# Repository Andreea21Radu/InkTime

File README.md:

# InkTime - Smartwatch PCB Design

**Autor:** Radu Andreea
**Licenta:** Apache License 2.0 

## 1. Arhitectura sistemului

Sistemul este construit in jurul microcontroller-ului **nRF52840**, care gestioneaza comunicatia si perifericele.

Structura generala este urmatoarea:

## 2. BOM (Bill of Materials)

## CIRCUITE INTEGRATE (IC)

| Componentă | JLC Part # | Package | Descriere | Datasheet |
| :--- | :--- | :--- | :--- | :--- |
| IC1 | C3682423 | DSBGA-8 (1.6x1.1) | Încărcător baterie Li-Ion / Li-Polymer | [datasheet](https://www.ti.com/cn/lit/ds/symlink/bq25180.pdf) |
| IC2 | C81079 | DSBGA-9 | Driver haptic ERM/LRA | [datasheet](https://www.ti.com/cn/lit/gpn/drv2605) |
| IC3 | C189517 | LGA-12 (2x2) | Accelerometru 3 axe low-g 12bit | [datasheet](https://www.lcsc.com/datasheet/C189517.pdf) |
| IC9 | C7065276 | WLCSP-15B (2.3x1.4) | DC-DC buck-boost regulator I2C | [datasheet](https://wmsc.lcsc.com/wmsc/upload/file/pdf/v2/lcsc/2312271436_Richtek-Tech-RT6160AWSC_C7065276.pdf) |
| U1 | C3606653 | QFN-48 (6x6) | nRF52840 MCU | [datasheet](https://www.lcsc.com/datasheet/C3606653.pdf) |
| U2 | C2682616 | DFN-8-EP (2x2) | Fuel gauge baterie Li-Ion I2C | [datasheet](https://www.lcsc.com/datasheet/lcsc_datasheet_2410121738_Analog-Devices-Inc--Maxim-Integrated-MAX17048G-T10_C2682616.pdf) |

---

## CONECTORI

| Componentă | JLC Part # | Package | Descriere | Datasheet |
| :--- | :--- | :--- | :--- | :--- |
| J1 | C122434 | SMD, FFC/FPC 0.5mm | Conector FPC 24 pini, unghi drept | [datasheet](https://www.molex.com/content/dam/molex/molex-dot-com/products/automated/en-us/salesdrawingpdf/503/503480/5034802400_sd.pdf) |
| J2 | C90533 | 1mm pitch | Adaptor cablu 6 poziții | [datasheet](https://wmsc.lcsc.com/wmsc/upload/file/pdf/v2/lcsc/1810141506_LX-FFC6P1-0mm7CM_C90533.pdf) |
| J4 | C709357 | USB-C SMD | Conector USB Type-C 16P | [datasheet](https://www.lcsc.com/datasheet/lcsc_datasheet_2404191039_Shenzhen-Kinghelm-Elec-KH-TYPE-C-16P_C709357.pdf) |

---

## SEMICONDUCTORI

| Componentă | JLC Part # | Package | Descriere | Datasheet |
| :--- | :--- | :--- | :--- | :--- |
| Q1 | C2564 | TO-220AB | MOSFET P-channel 55V 74A | [datasheet](https://www.lcsc.com/datasheet/lcsc_datasheet_1809041724_Infineon-Technologies-IRF4905PBF_C2564.pdf) |
| Q3 | C469327 | SOT-323 | MOSFET N-channel 30V 1.5A | [datasheet](https://www.lcsc.com/datasheet/lcsc_datasheet_1912202016_Vishay-Intertech-SI1308EDL-T1-GE3_C469327.pdf) |
| D2, D4, D5 | C82046 | SOD-123 | Diodă Schottky 0.5A 30V | [datasheet](https://www.lcsc.com/datasheet/lcsc_datasheet_2304140030_onsemi-MBR0530T1G_C82046.pdf) |
| D3 | C2969755 | SOT-23-6L | Protecție ESD USB | [datasheet](https://wmsc.lcsc.com/wmsc/upload/file/pdf/v2/lcsc/2211080730_STMicroelectronics-USBLC6-2SC6Y_C2969755.pdf) |

---

## INDUCTORI

| Componentă | JLC Part # | Package | Descriere | Datasheet |
| :--- | :--- | :--- | :--- | :--- |
| L1, L2, L3 | C12669 | 0402 | Inductor general (chip inductor) | [datasheet](https://www.lcsc.com/datasheet/lcsc_datasheet_2304140030_Murata-Electronics-LQG15HS27NJ02D_C12669.pdf) |
| L5 | C1329646 | SMD 4.8x4.8mm | Power inductor 4.7µH 1.6A | [datasheet](https://wmsc.lcsc.com/wmsc/upload/file/pdf/v2/lcsc/2304140030_BOURNS-SRR4828A-4R7Y_C1329646.pdf) |
| L7 | C5832368 | 1008 | Power inductor 470nH 6.5A | [datasheet](https://wmsc.lcsc.com/wmsc/upload/file/pdf/v2/lcsc/2306021632_cjiang--Changjiang-Microelectronics-Tech-FTC252012SR47MBCA_C5832368.pdf) |

---

## CRISTALE

| Componentă | JLC Part # | Package | Descriere | Datasheet |
| :--- | :--- | :--- | :--- | :--- |
| X1 | C9009 | SMD3225-4P | Cristal Oscilator 32 MHz | [datasheet](https://www.lcsc.com/datasheet/lcsc_datasheet_2403291504_YXC-Crystal-Oscillators-X322532MOB4SI_C9009.pdf) |
| X2 | C32346 | SMD3215-2P | Cristal Oscilator 32.768 kHz | [datasheet](https://www.lcsc.com/datasheet/lcsc_datasheet_2404180925_Seiko-Epson-Q13FC13500004_C32346.pdf) |

---

## REZISTOARE

| Componentă | JLC Part # | Package | Descriere | Datasheet |
| :--- | :--- | :--- | :--- | :--- |
| R1_EP_DR | C3920633 | 0201 | 7.68kΩ Thin Film ±0.5% | [datasheet](https://wmsc.lcsc.com/wmsc/upload/file/pdf/v2/lcsc/2404081048_TE-Connectivity-CPF0201B511RE1_C3920633.pdf) |
| R1_USB, R2_USB | C3920633 | 0201 | 7.68kΩ Thin Film ±0.5% | [datasheet](https://wmsc.lcsc.com/wmsc/upload/file/pdf/v2/lcsc/2404081048_TE-Connectivity-CPF0201B511RE1_C3920633.pdf) |
| R2, R3, R4 | C3920633 | 0201 | 7.68kΩ Thin Film ±0.5% | [datasheet](https://wmsc.lcsc.com/wmsc/upload/file/pdf/v2/lcsc/2404081048_TE-Connectivity-CPF0201B511RE1_C3920633.pdf) |
| R2_EP_DR, R9, R_PWR_EPD | C3920633 | 0201 | 7.68kΩ Thin Film ±0.5% | [datasheet](https://wmsc.lcsc.com/wmsc/upload/file/pdf/v2/lcsc/2404081048_TE-Connectivity-CPF0201B511RE1_C3920633.pdf) |
| R5, R7, R8 | C3920633 | 0201 | 7.68kΩ Thin Film ±0.5% | [datasheet](https://wmsc.lcsc.com/wmsc/upload/file/pdf/v2/lcsc/2404081048_TE-Connectivity-CPF0201B511RE1_C3920633.pdf) |
| R17, R18 | C3920633 | 0201 | 7.68kΩ Thin Film ±0.5% | [datasheet](https://wmsc.lcsc.com/wmsc/upload/file/pdf/v2/lcsc/2404081048_TE-Connectivity-CPF0201B511RE1_C3920633.pdf) |
| R_TYPE_SEL | C3920633 | 0201 | 7.68kΩ Thin Film ±0.5% | [datasheet](https://wmsc.lcsc.com/wmsc/upload/file/pdf/v2/lcsc/2404081048_TE-Connectivity-CPF0201B511RE1_C3920633.pdf) |

---

## CAPACITORI

| Componentă | JLC Part # | Package | Descriere | Datasheet |
| :--- | :--- | :--- | :--- | :--- |
| C1, C2, C17, C18 | C9900156064 | 0201 | Generic chip capacitor | [datasheet](https://ds.yuden.co.jp/TYCOMPAS/or/download?pn=MLAST063SCG681JFNA01&fileType=CA) |
| C1-EP-DR | C9900156064 | 0201 | Generic chip capacitor | [datasheet](https://ds.yuden.co.jp/TYCOMPAS/or/download?pn=MLAST063SCG681JFNA01&fileType=CA) |
| C2-EP-DR | C9900156064 | 0201 | Generic chip capacitor | [datasheet](https://ds.yuden.co.jp/TYCOMPAS/or/download?pn=MLAST063SCG681JFNA01&fileType=CA) |
| C3, C4 | C9900156064 | 0201 | Generic chip capacitor | [datasheet](https://ds.yuden.co.jp/TYCOMPAS/or/download?pn=MLAST063SCG681JFNA01&fileType=CA) |
| C5, C7, C8, C12, C19 | C9900156064 | 0201 | Generic chip capacitor | [datasheet](https://ds.yuden.co.jp/TYCOMPAS/or/download?pn=MLAST063SCG681JFNA01&fileType=CA) |
| C6, C14, C20, C21 | C9900156064 | 0201 | Generic chip capacitor | [datasheet](https://ds.yuden.co.jp/TYCOMPAS/or/download?pn=MLAST063SCG681JFNA01&fileType=CA) |
| C9 | C9900156064 | 0201 | Generic chip capacitor | [datasheet](https://ds.yuden.co.jp/TYCOMPAS/or/download?pn=MLAST063SCG681JFNA01&fileType=CA) |
| C10, C13, C22 | C9900156064 | 0201 | Generic chip capacitor | [datasheet](https://ds.yuden.co.jp/TYCOMPAS/or/download?pn=MLAST063SCG681JFNA01&fileType=CA) |
| C11 | C9900156064 | 0201 | Generic chip capacitor | [datasheet](https://ds.yuden.co.jp/TYCOMPAS/or/download?pn=MLAST063SCG681JFNA01&fileType=CA) |
| C15 | C9900156064 | 0201 | Generic chip capacitor | [datasheet](https://ds.yuden.co.jp/TYCOMPAS/or/download?pn=MLAST063SCG681JFNA01&fileType=CA) |
| C16 | C9900156064 | 0201 | Generic chip capacitor | [datasheet](https://ds.yuden.co.jp/TYCOMPAS/or/download?pn=MLAST063SCG681JFNA01&fileType=CA) |
| C23, C27, C34, C42 | C21012218 | 0402 | Capacitor ceramic | [datasheet](https://jlc-prod-smt.oss-eu-central-1.aliyuncs.com/smtDataManualFile/8603520985945550848-C21012218.pdf) |
| C24, C39 | C9900179830 | 0402 | Capacitor ceramic | N/A |
| C25, C33 | C9900179830 | 0402 | Capacitor ceramic | N/A |
| C29, C30, C31, C32, C37, C38 | C3920633 | 0201 | Capacitor ceramic | [datasheet](https://ds.yuden.co.jp/TYCOMPAS/or/download?pn=MLAST063SCG681JFNA01&fileType=CA) |
| C43 | C9900156064 | 0201 | Generic chip capacitor | [datasheet](https://ds.yuden.co.jp/TYCOMPAS/or/download?pn=MLAST063SCG681JFNA01&fileType=CA) |
| EPD_C1, EPD_C2, EPD_C6, EPD_C7, EPD_C8, EPD_C9, EPD_C10, EPD_C11, EPD_C12 | C9900156064 | 0201 | Generic chip capacitor | [datasheet](https://ds.yuden.co.jp/TYCOMPAS/or/download?pn=MLAST063SCG681JFNA01&fileType=CA) |
| EPD_C5 | C9900156064 | 0201 | Generic chip capacitor | [datasheet](https://ds.yuden.co.jp/TYCOMPAS/or/download?pn=MLAST063SCG681JFNA01&fileType=CA) |

---

## ALTE COMPONENTE

| Componentă | JLC Part # | Package | Descriere | Datasheet |
| :--- | :--- | :--- | :--- | :--- |
| ANT1 | C2917717 | 1206 | Antenă Patch 2.4 GHz | [datasheet](https://www.lcsc.com/datasheet/lcsc_datasheet_2404021210_Johanson-Dielectrics-2450AT18B100E_C2917717.pdf) |
| SJ1 | N/A | Solder Jumper | SMD solder JUMPER (leave open) | N/A |
| SW_DN, SW_ENT, SW_UP | C569760 | SMD 3.9x2.9mm | Buton tactil SPST (Tactile Switch) | [datasheet](https://wmsc.lcsc.com/wmsc/upload/file/pdf/v2/lcsc/2301111010_PANASONIC-EVPAKE31A_C569760.pdf) |
| TP (Test Pads) | N/A | N/A | Puncte de testare (Test pads) | N/A |

## 3. Functionalitate hardware si specificatii tehnice

Proiectul **InkTime** reprezinta un dispozitiv wearable optimizat pentru consum redus de energie, capabil sa functioneze pe perioade lungi de timp datorita combinatiei dintre un microcontroller eficient si un display E-Ink, care consuma energie doar la actualizare.

---

### 3.1 Unitatea centrala (Microcontroller)

In centrul sistemului se afla circuitul **nRF52840**, care integreaza toate functiile principale:

* Procesor **ARM Cortex-M4F la 64 MHz**, suficient pentru procesare de semnale si control periferice
* Suport integrat pentru **Bluetooth Low Energy (BLE)**, utilizat pentru comunicarea cu telefonul
* Moduri de consum redus (sleep si deep sleep), unde curentul scade pana la nivel de microamperi

Acest microcontroller permite rularea simultana a comunicatiei wireless si a interactiunii cu senzorii, mentinand consumul scazut.

### 3.2 Sistem de alimentare

Alimentarea este realizata printr-un lant complet de power management:

* **BQ25180** – responsabil pentru incarcarea bateriei Li-Po prin USB-C, folosind metoda CC/CV si protectii integrate
* **RT6160** – convertor buck-boost care asigura o tensiune stabila de **3.3V**, chiar daca bateria scade sub aceasta valoare
* **MAX17048** – circuit de monitorizare a bateriei, care transmite starea de incarcare catre microcontroller prin I2C

Avantajul folosirii convertorului buck-boost este utilizarea eficienta a bateriei pe intreaga plaja de tensiuni.

### 3.3 Comunicatia intre module

Pentru conectarea componentelor, sistemul foloseste doua interfete principale:

#### Magistrala I2C

Este utilizata pentru perifericele inteligente:

* accelerometrul (IMU)
* fuel gauge-ul
* driverul haptic

Toate aceste componente sunt conectate pe aceeasi magistrala, ceea ce reduce numarul de pini folositi si simplifica traseele pe PCB.

#### Magistrala SPI

Este dedicata exclusiv display-ului:

* display-ul E-Ink este conectat prin SPI folosind conectorul FPC
* aceasta interfata permite transfer rapid de date necesar actualizarii imaginii

### 3.4 Interactiune cu utilizatorul

Dispozitivul include:

* 3 butoane pentru navigare (UP, ENTER, DOWN)
* feedback haptic realizat cu **DRV2605**, controlat prin PWM

Acest sistem permite interactiune intuitiva fara consum mare de energie.

### 3.5 Estimarea consumului de energie

Sistemul este alimentat de o baterie Li-Po de aproximativ **250 mAh**.

Consum estimat:

* Sleep (MCU + BLE): ~35 µA
* Functionare activa (citire senzori): ~120 µA
* Actualizare display: ~25 µA

Curent mediu total:

I_avg ≈ 180 µA = 0.18 mA

### 3.6 Autonomie estimata

Autonomia teoretica:

T = 250 mAh / 0.18 mA ≈ 1380 ore

In conditii reale (BLE, senzori, vibratii):

👉 aproximativ **9 – 14 zile**

## 4. Mapare pini nRF52840

### 4.1 Alocarea pinilor

| Componenta    | Semnal | Pin nRF | Directie | Motiv                |
| ------------- | ------ | ------- | -------- | -------------------- |
| Display E-Ink | SCK    | P0.11   | Output   | Clock SPI            |
| Display E-Ink | MOSI   | P0.12   | Output   | Transfer date        |
| Display E-Ink | CS     | P0.13   | Output   | Selectie dispozitiv  |
| Display E-Ink | DC     | P0.14   | Output   | Data / Command       |
| Display E-Ink | RESET  | P0.15   | Output   | Reset hardware       |
| Display E-Ink | BUSY   | P0.16   | Input    | Status display       |
| I2C           | SDA    | P0.26   | I/O      | Linie date           |
| I2C           | SCL    | P0.27   | Output   | Linie clock          |
| Buton UP      | GPIO   | P1.07   | Input    | Navigare             |
| Buton ENTER   | GPIO   | P1.08   | Input    | Confirmare           |
| Buton DOWN    | GPIO   | P1.09   | Input    | Navigare             |
| Motor haptic  | PWM    | P1.02   | Output   | Control vibratii     |
| RT6160        | EN     | P0.18   | Output   | Activare convertor   |
| IMU           | INT    | P0.25   | Input    | Intrerupere hardware |

---

### 4.2 Decizii de design

* **Port 0** a fost folosit pentru interfete rapide (SPI, I2C)
* **Port 1** a fost folosit pentru butoane, pentru a evita interferente
* pinii SPI au fost grupati fizic pentru trasee mai scurte
* magistrala I2C este comuna pentru mai multe dispozitive → economie de pini
* pinii NFC (P0.09, P0.10) au fost evitati pentru extensii viitoare

## 5. Design log si decizii de implementare

### 5.1 Layout PCB

* componentele au fost plasate compact
* traseele de alimentare au fost facute la **0.3 mm**
* traseele de semnal la **0.15 mm**
* zona antenei a fost lasata fara cupru

### 5.2 Probleme si solutii

* componente 0201 → necesare pentru spatiu redus
* routing dificil sub MCU → s-au folosit trasee mai subtiri local
* antena → zona keep-out pentru performanta RF

### 5.3 Integritate semnal

* condensatori de decuplare (100nF) plasati foarte aproape de pini
* GND realizat cu polygon pour pe ambele straturi
* via stitching pentru masa

## 6. Randari si imagini

(Imaginile se gasesc in folderul `Images`)

* vedere PCB top
* vedere PCB bottom
* randare 3D
* vedere explodata

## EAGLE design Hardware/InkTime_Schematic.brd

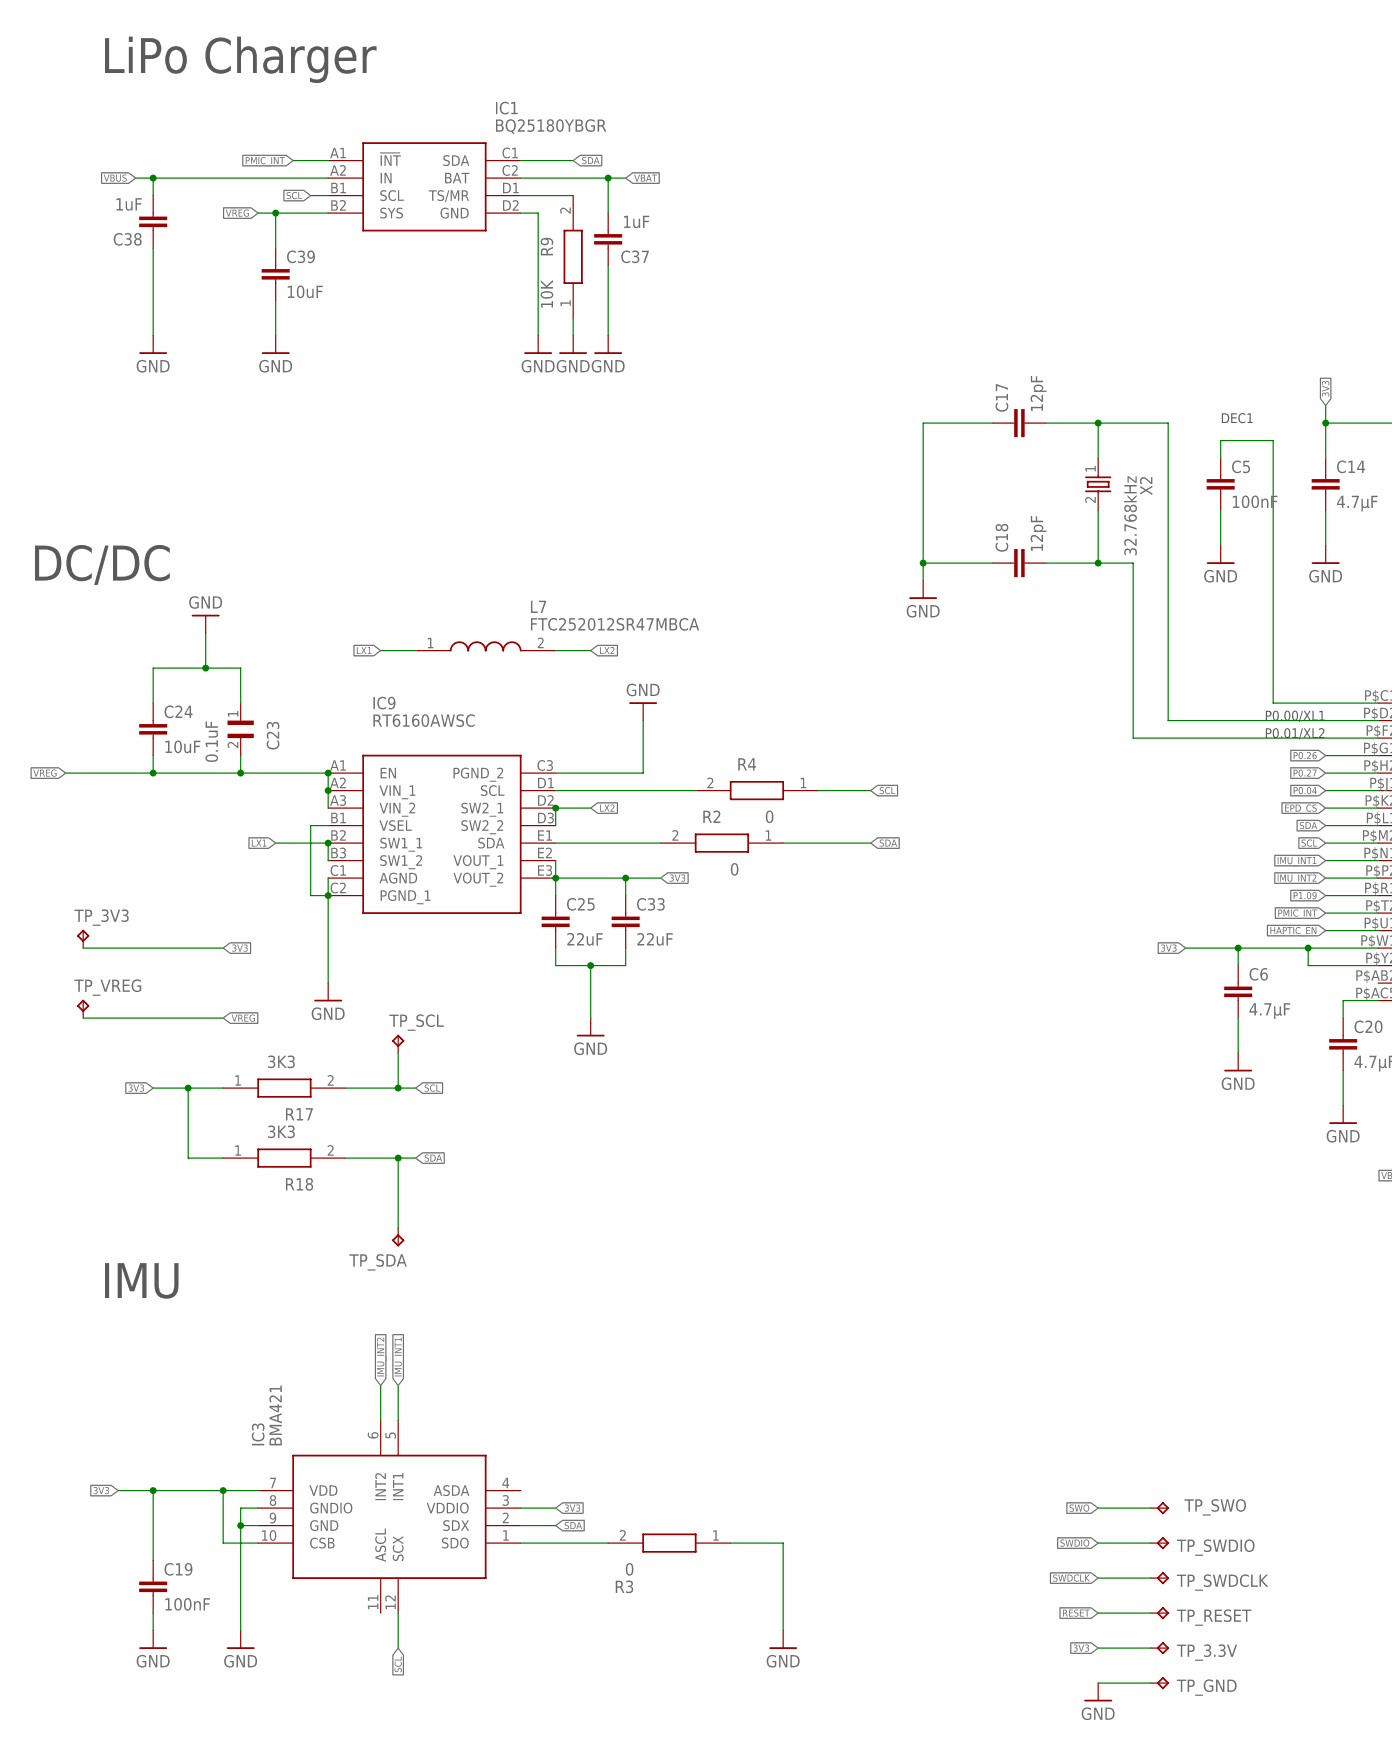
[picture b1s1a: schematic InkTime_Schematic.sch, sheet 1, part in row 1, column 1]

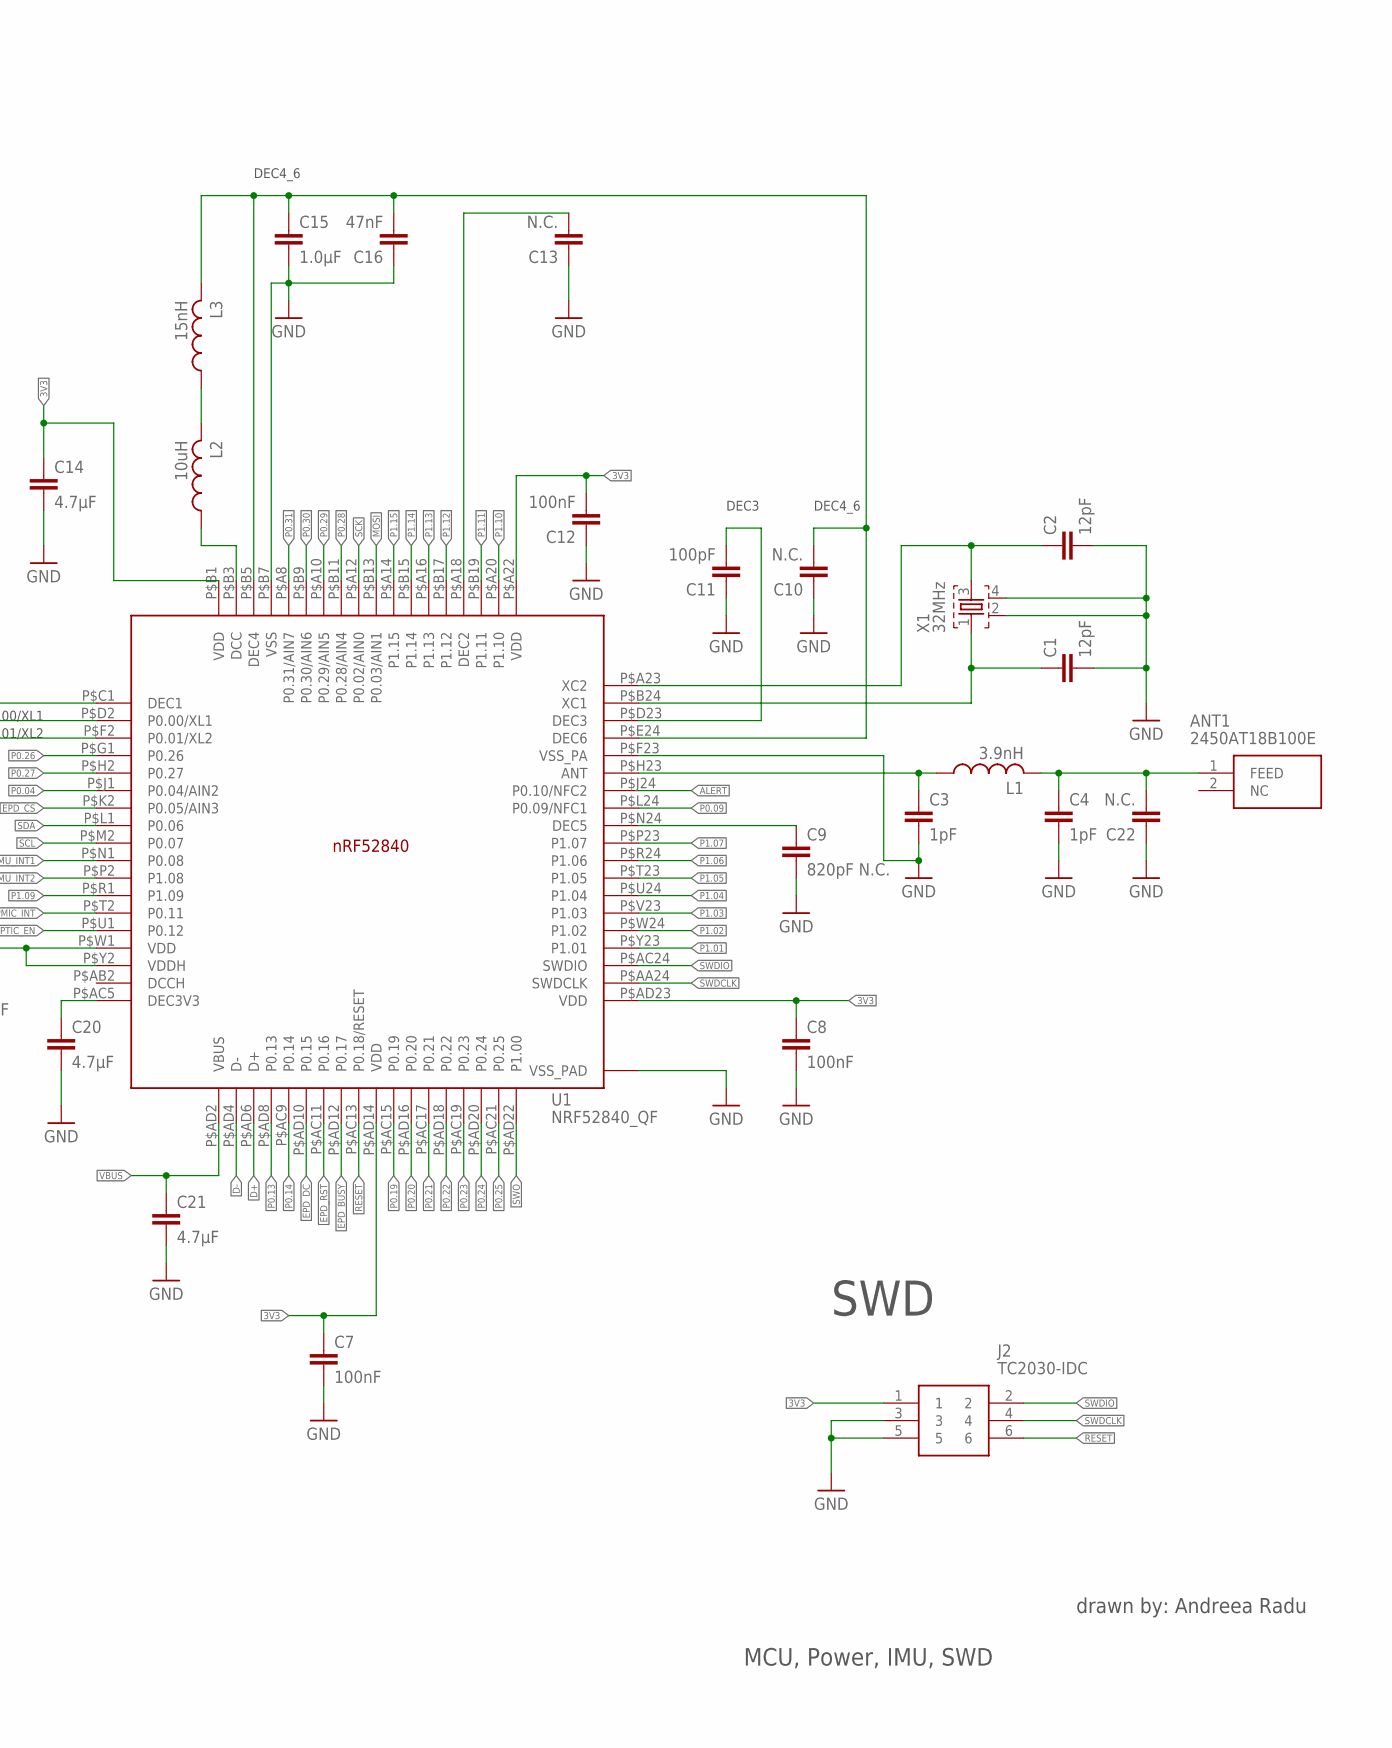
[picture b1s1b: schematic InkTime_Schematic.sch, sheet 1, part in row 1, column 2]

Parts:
ANT1: 2450AT18B100E; 2450AT18B100E_ANTC3216X140N
C1, C2, C17, C18: 12pF; NORDIC_NRF_3_RESC0201_L
C3, C4: 1pF; NORDIC_NRF_3_RESC0201_L
C5, C7, C8, C12, C19: 100nF; NORDIC_NRF_3_RESC0201_L
C6, C14, C20, C21: 4.7μF; ESP32_C6_LIBRARY_1_ESP32_WROVER_EAGLE-LTSPICE_C0402
C9: 820pF N.C.; NORDIC_NRF_3_RESC0201_L
C10, C13, C22: N.C.; NORDIC_NRF_3_RESC0201_L
C11: 100pF; NORDIC_NRF_3_RESC0201_L
C15: 1.0μF; ESP32_C6_LIBRARY_1_ESP32_WROVER_EAGLE-LTSPICE_C0402
C16: 47nF; NORDIC_NRF_3_RESC0201_L
C23: 0.1uF; GRM011R60J152KE01L_2_CAPC0201X13N
C24, C39: 10uF; ESP32_C6_LIBRARY_1_ESP32_WROVER_EAGLE-LTSPICE_C0402
C25, C33: 22uF; ESP32_C6_LIBRARY_1_ESP32_WROVER_EAGLE-LTSPICE_C0402
C37, C38: 1uF; ESP32_C6_LIBRARY_1_ESP32_WROVER_EAGLE-LTSPICE_C0402
IC1: BQ25180YBGR; BQ25180YBGR_BGA8C40P2X4_100X155X50
IC3: BMA421; BMA423_BMA423
IC9: RT6160AWSC; RT6160AWSC_BGA15C40P3X5_140X230X60
J2: TC2030-IDC; TC2030-IDC_TC2030IDC
L1: 3.9nH; NORDIC_NRF_2_RESC0402_L
L2: 10uH; NORDIC_NRF_2_RESC0402_L
L3: 15nH; NORDIC_NRF_2_RESC0402_L
L7: FTC252012SR47MBCA; MLP2016SR47MT0S1_INDC2016X100N
R2, R3, R4: 0; CPF0201D7K68C1_0201
R9: 10K; CPF0201D7K68C1_0201
R17, R18: 3K3; CPF0201D7K68C1_0201
TP_3.3V, TP_3V3: HECTOR_WATCH_1_TPTP20R; HECTOR_WATCH_1_TP20R
TP_GND: HECTOR_WATCH_1_TPTP20R; HECTOR_WATCH_1_TP20R
TP_RESET: HECTOR_WATCH_1_TPTP20R; HECTOR_WATCH_1_TP20R
TP_SCL: HECTOR_WATCH_1_TPTP20R; HECTOR_WATCH_1_TP20R
TP_SDA: HECTOR_WATCH_1_TPTP20R; HECTOR_WATCH_1_TP20R
TP_SWDCLK: HECTOR_WATCH_1_TPTP20R; HECTOR_WATCH_1_TP20R
TP_SWDIO: HECTOR_WATCH_1_TPTP20R; HECTOR_WATCH_1_TP20R
TP_SWO: HECTOR_WATCH_1_TPTP20R; HECTOR_WATCH_1_TP20R
TP_VREG: HECTOR_WATCH_1_TPTP20R; HECTOR_WATCH_1_TP20R
U1: NRF52840_QF; NORDIC_NRF_4_AQFN50P700X700X85_HS-74N
X1: 32MHz; NORDIC_NRF_BT-XTAL_2016_N
X2: 32.768kHz; NORDIC_NRF_1_XTAL_3215_N

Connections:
3V3: C6.1, C7.1, C8.1, C12.2, C14.1, C19.1, C25.1, C33.1, IC3.3 (VDDIO), IC3.7 (VDD), IC3.10 (CSB), IC9.E2 (VOUT_1), IC9.E3 (VOUT_2), J2.1, R17.1, R18.1, TP_3.3V.TP, TP_3V3.TP, U1.P$A22 (VDD), U1.P$AD14 (VDD), U1.P$AD23 (VDD), U1.P$B1 (VDD), U1.P$W1 (VDD), U1.P$Y2 (VDDH); also elsewhere on the board
ALERT: U1.P$J24 (P0.10/NFC2); also elsewhere on the board
D+: U1.P$AD6 (D+); also elsewhere on the board
D-: U1.P$AD4 (D-); also elsewhere on the board
EPD_BUSY: U1.P$AD12 (P0.17); also elsewhere on the board
EPD_CS: U1.P$K2 (P0.05/AIN3); also elsewhere on the board
EPD_DC: U1.P$AD10 (P0.15); also elsewhere on the board
EPD_RST: U1.P$AC11 (P0.16); also elsewhere on the board
GND: C1.2, C2.2, C3.2, C4.2, C5.2, C6.2, C7.2, C8.2, C9.2, C10.1, C11.1, C12.1, C13.1, C14.2, C15.2, C16.1, C17.1, C18.1, C19.2, C20.2, C21.2, C22.1, C23.1, C24.1, C25.2, C33.2, C37.1, C38.1, C39.2, IC1.D2 (GND), IC3.8 (GNDIO), IC3.9 (GND), IC9.B1 (VSEL), IC9.C1 (AGND), IC9.C2 (PGND_1), IC9.C3 (PGND_2), J2.3, J2.5, R3.1, R9.1, TP_GND.TP, U1.P$74 (VSS_PAD), U1.P$75 (VSS_PAD), U1.P$76 (VSS_PAD), U1.P$77 (VSS_PAD), U1.P$78 (VSS_PAD), U1.P$79 (VSS_PAD), U1.P$80 (VSS_PAD), U1.P$81 (VSS_PAD), U1.P$82 (VSS_PAD), U1.P$83 (VSS_PAD), U1.P$84 (VSS_PAD), U1.P$85 (VSS_PAD), U1.P$86 (VSS_PAD), U1.P$87 (VSS_PAD), U1.P$88 (VSS_PAD), U1.P$89 (VSS_PAD), U1.P$90 (VSS_PAD), U1.P$B7 (VSS), U1.P$F23 (VSS_PA), X1.2, X1.4; also elsewhere on the board
HAPTIC_EN: U1.P$U1 (P0.12); also elsewhere on the board
IMU_INT1: IC3.5 (INT1), U1.P$N1 (P0.08)
IMU_INT2: IC3.6 (INT2), U1.P$P2 (P1.08)
LX1: IC9.B2 (SW1_1), IC9.B3 (SW1_2), L7.1
LX2: IC9.D2 (SW2_1), IC9.D3 (SW2_2), L7.2
MOSI: U1.P$B13 (P0.03/AIN1); also elsewhere on the board
unnamed: C5.1, U1.P$C1 (DEC1)
unnamed: IC1.D1 (TS/MR), R9.2
unnamed: IC9.D1 (SCL), R4.2
unnamed: IC9.E1 (SDA), R2.2
unnamed: IC3.1 (SDO), R3.2
unnamed: C20.1, U1.P$AC5 (DEC3V3)
unnamed: C9.1, U1.P$N24 (DEC5)
unnamed: C3.1, L1.1, U1.P$H23 (ANT)
unnamed: ANT1.1 (FEED), C4.1, C22.2, L1.2
unnamed: L2.1, U1.P$B3 (DCC)
unnamed: L2.2, L3.1
unnamed: C10.2, C15.1, C16.2, L3.2, U1.P$B5 (DEC4), U1.P$E24 (DEC6)
unnamed: C13.2, U1.P$A18 (DEC2)
unnamed: C11.2, U1.P$D23 (DEC3)
unnamed: C2.1, U1.P$A23 (XC2), X1.3
unnamed: C1.1, U1.P$B24 (XC1), X1.1
unnamed: C17.2, U1.P$D2 (P0.00/XL1), X2.1
unnamed: C18.2, U1.P$F2 (P0.01/XL2), X2.2
P0.04: U1.P$J1 (P0.04/AIN2)
P0.09: U1.P$L24 (P0.09/NFC1)
P0.13: U1.P$AD8 (P0.13); also elsewhere on the board
P0.14: U1.P$AC9 (P0.14); also elsewhere on the board
P0.19: U1.P$AC15 (P0.19)
P0.20: U1.P$AD16 (P0.20)
P0.21: U1.P$AC17 (P0.21)
P0.22: U1.P$AD18 (P0.22)
P0.23: U1.P$AC19 (P0.23)
P0.24: U1.P$AD20 (P0.24)
P0.25: U1.P$AC21 (P0.25)
P0.26: U1.P$G1 (P0.26)
P0.27: U1.P$H2 (P0.27)
P0.28: U1.P$B11 (P0.28/AIN4)
P0.29: U1.P$A10 (P0.29/AIN5)
P0.30: U1.P$B9 (P0.30/AIN6)
P0.31: U1.P$A8 (P0.31/AIN7)
P1.01: U1.P$Y23 (P1.01); also elsewhere on the board
P1.02: U1.P$W24 (P1.02); also elsewhere on the board
P1.03: U1.P$V23 (P1.03)
P1.04: U1.P$U24 (P1.04)
P1.05: U1.P$T23 (P1.05)
P1.06: U1.P$R24 (P1.06)
P1.07: U1.P$P23 (P1.07)
P1.09: U1.P$R1 (P1.09)
P1.10: U1.P$A20 (P1.10)
P1.11: U1.P$B19 (P1.11)
P1.12: U1.P$B17 (P1.12)
P1.13: U1.P$A16 (P1.13)
P1.14: U1.P$B15 (P1.14)
P1.15: U1.P$A14 (P1.15)
PMIC_INT: IC1.A1 (!INT), U1.P$T2 (P0.11)
RESET: J2.6, TP_RESET.TP, U1.P$AC13 (P0.18/RESET)
SCK: U1.P$A12 (P0.02/AIN0); also elsewhere on the board
SCL: IC1.B1 (SCL), IC3.12 (SCX), R4.1, R17.2, TP_SCL.TP, U1.P$M2 (P0.07); also elsewhere on the board
SDA: IC1.C1 (SDA), IC3.2 (SDX), R2.1, R18.2, TP_SDA.TP, U1.P$L1 (P0.06); also elsewhere on the board
SWDCLK: J2.4, TP_SWDCLK.TP, U1.P$AA24 (SWDCLK)
SWDIO: J2.2, TP_SWDIO.TP, U1.P$AC24 (SWDIO)
SWO: TP_SWO.TP, U1.P$AD22 (P1.00)
VBAT: C37.2, IC1.C2 (BAT); also elsewhere on the board
VBUS: C21.1, C38.2, IC1.A2 (IN), U1.P$AD2 (VBUS); also elsewhere on the board
VREG: C23.2, C24.2, C39.1, IC1.B2 (SYS), IC9.A1 (EN), IC9.A2 (VIN_1), IC9.A3 (VIN_2), TP_VREG.TP

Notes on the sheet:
MCU, Power, IMU, SWD
drawn by: Andreea Radu
LiPo Charger
DC/DC
IMU
DEC1
DEC4_6
DEC3
P0.00/XL1
P0.01/XL2
SWD

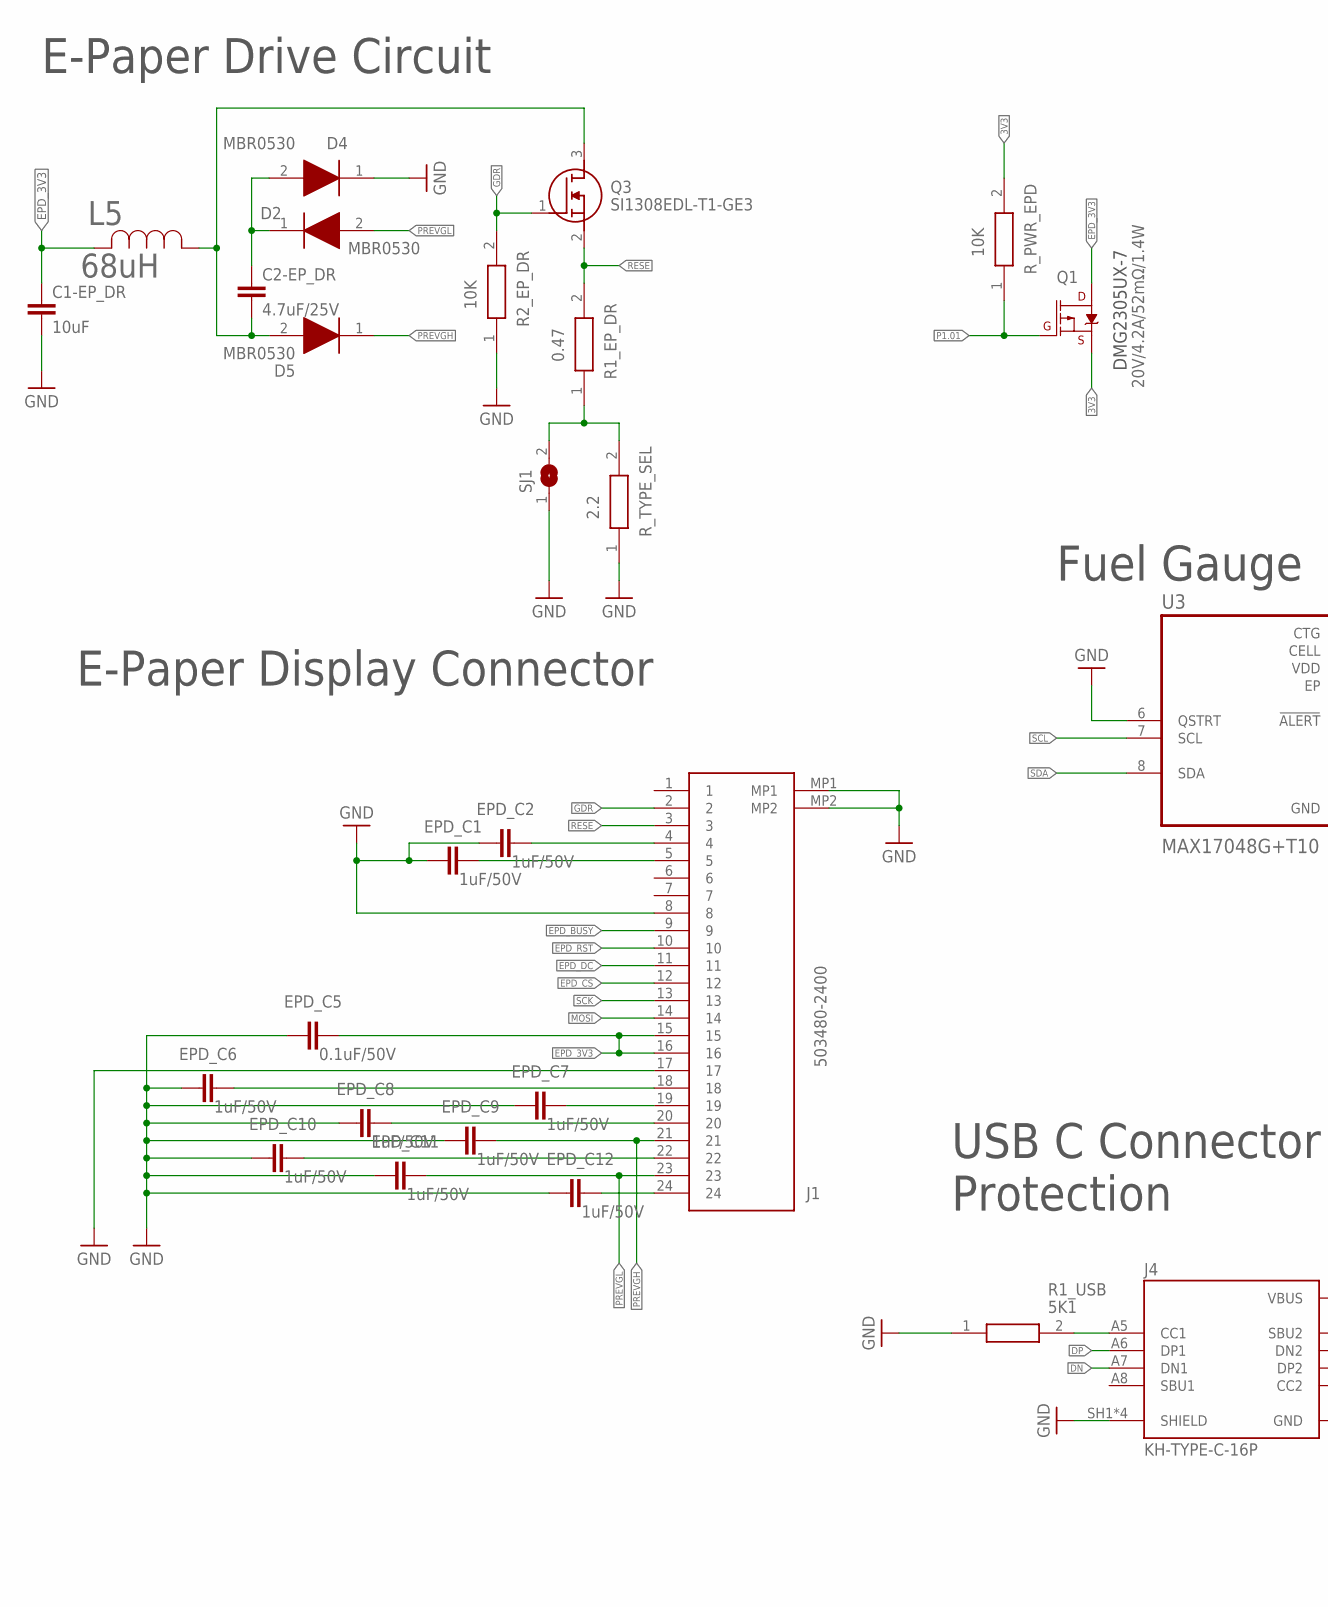
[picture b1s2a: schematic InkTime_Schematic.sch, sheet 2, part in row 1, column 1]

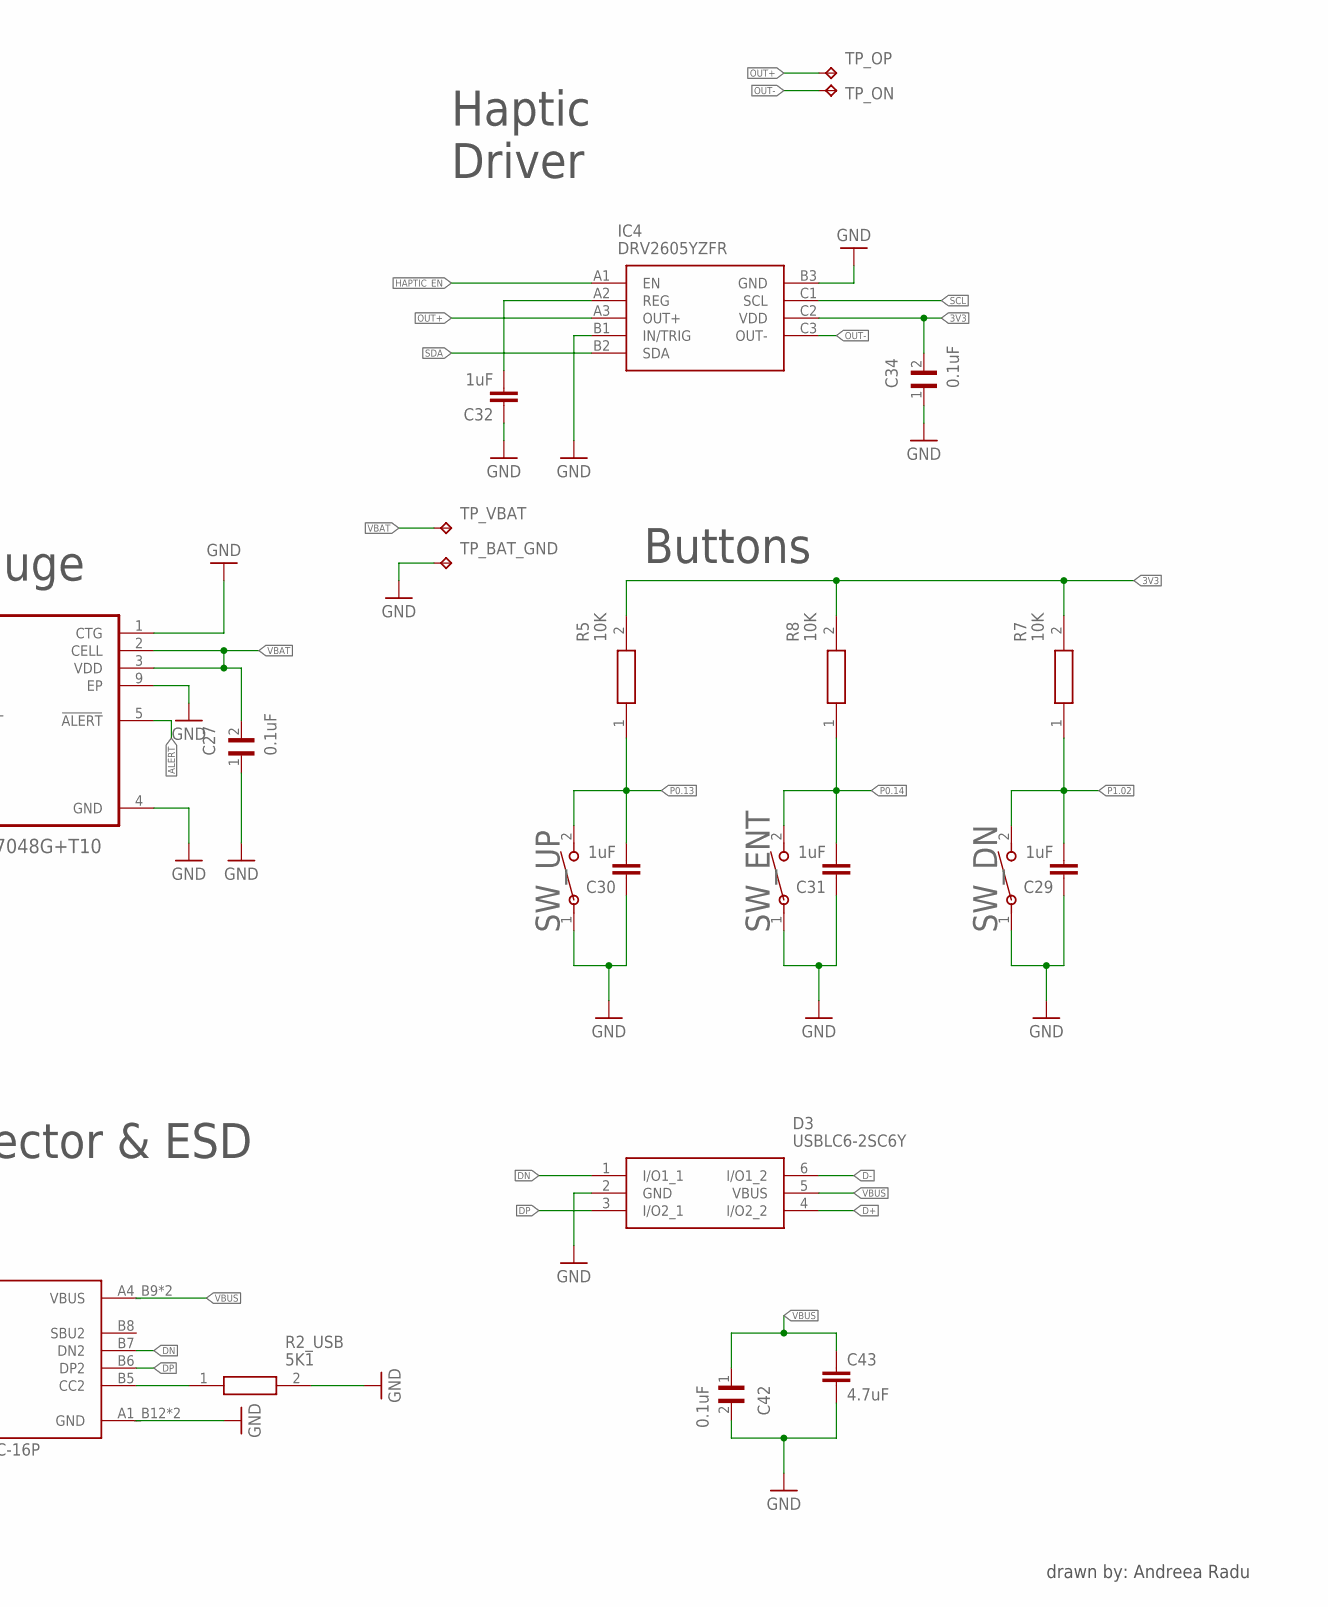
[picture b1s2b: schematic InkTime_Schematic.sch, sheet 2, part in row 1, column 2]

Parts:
C1-EP_DR: 10uF; ESP32_C6_LIBRARY_1_ESP32_WROVER_EAGLE-LTSPICE_C0402
C2-EP_DR: 4.7uF/25V; ESP32_C6_LIBRARY_1_ESP32_WROVER_EAGLE-LTSPICE_C0402
C27, C34, C42: 0.1uF; GRM011R60J152KE01L_2_CAPC0201X13N
C29, C30, C31, C32: 1uF; ESP32_C6_LIBRARY_1_ESP32_WROVER_EAGLE-LTSPICE_C0402
C43: 4.7uF; ESP32_C6_LIBRARY_1_ESP32_WROVER_EAGLE-LTSPICE_C0402
D2, D4, D5: MBR0530; ESP32_C6_LIBRARY_5_SOD3716X135N
D3: USBLC6-2SC6Y; ESP32_C6_LIBRARY_3_SOT95P280X145-6N
EPD_C1, EPD_C2, EPD_C6, EPD_C7, EPD_C8, EPD_C9, EPD_C10, EPD_C11, EPD_C12: 1uF/50V; ESP32_C6_LIBRARY_1_ESP32_WROVER_EAGLE-LTSPICE_C0402
EPD_C5: 0.1uF/50V; NORDIC_NRF_3_RESC0201_L
IC4: DRV2605YZFR; DRV2605YZFR_BGA9C50P3X3_144X144X62
J1: 503480-2400; 503480-2400_5034802400
J4: KH-TYPE-C-16P; KH-TYPE-C-16P_KINGHELM_KH-TYPE-C-16P
L5: 68uH; ESP32_C6_LIBRARY_2_IND_4828-WE-TPC_WRE
Q1: 20V/4.2A/52mΩ/1.4W; ESP32_C6_LIBRARY_4_ESP32_C6_LIBRARY_4_ESP32_C6_LIBRARY_4_ES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
Q3: SI1308EDL-T1-GE3; ESP32_C6_LIBRARY_6_SOT65P210X110-3N
R1_EP_DR: 0.47; CPF0201D7K68C1_0201
R1_USB, R2_USB: 5K1; ERA-1AEB3401C_0201
R2_EP_DR: 10K; CPF0201D7K68C1_0201
R5, R7, R8: 10K; ERA-1AEB3401C_0201
R_PWR_EPD: 10K; CPF0201D7K68C1_0201
R_TYPE_SEL: 2.2; CPF0201D7K68C1_0201
SJ1: ESP32_C6_LIBRARY_7_JUMPER_SJ
SW_DN: 2025-10-22_07-23-44_LIBRARY_EVP-AKE31ASW_EVP-AKE3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; 2025-10-22_07-23-44_LIBRARY_SW_EVP-AKE31A_PAN
SW_ENT: 2025-10-22_07-23-44_LIBRARY_EVP-AKE31ASW_EVP-AKE3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; 2025-10-22_07-23-44_LIBRARY_SW_EVP-AKE31A_PAN
SW_UP: 2025-10-22_07-23-44_LIBRARY_EVP-AKE31ASW_EVP-AKE3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; 2025-10-22_07-23-44_LIBRARY_SW_EVP-AKE31A_PAN
TP_BAT_GND: HECTOR_WATCH_1_TPTP20R; HECTOR_WATCH_1_TP20R
TP_ON: HECTOR_WATCH_1_TPTP20R; HECTOR_WATCH_1_TP20R
TP_OP: HECTOR_WATCH_1_TPTP20R; HECTOR_WATCH_1_TP20R
TP_VBAT: HECTOR_WATCH_1_TPTP20R; HECTOR_WATCH_1_TP20R
U3: MAX17048G+T10; ESP32_C6_LIBRARY_SON50P200X200X80-9N

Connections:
3V3: C34.2, IC4.C2 (VDD), Q1.2 (S), R5.2, R7.2, R8.2, R_PWR_EPD.2; also elsewhere on the board
ALERT: U3.5 (!ALERT); also elsewhere on the board
D+: D3.4 (I/O2_2); also elsewhere on the board
D-: D3.6 (I/O1_2); also elsewhere on the board
DN: D3.1 (I/O1_1), J4.A7 (DN1), J4.B7 (DN2)
DP: D3.3 (I/O2_1), J4.A6 (DP1), J4.B6 (DP2)
EPD_3V3: C1-EP_DR.1, EPD_C5.2, J1.15, J1.16, L5.2, Q1.3 (D)
EPD_BUSY: J1.9; also elsewhere on the board
EPD_CS: J1.12; also elsewhere on the board
EPD_DC: J1.11; also elsewhere on the board
EPD_RST: J1.10; also elsewhere on the board
GDR: J1.2, Q3.1 (G), R2_EP_DR.2
GND: C1-EP_DR.2, C27.1, C29.1, C30.1, C31.1, C32.1, C34.1, C42.2, C43.2, D3.2 (GND), D4.1 (K), EPD_C1.1, EPD_C2.1, EPD_C5.1, EPD_C6.1, EPD_C7.1, EPD_C8.1, EPD_C9.1, EPD_C10.1, EPD_C11.1, EPD_C12.1, IC4.B1 (IN/TRIG), IC4.B3 (GND), J1.8, J1.17, J1.MP1, J1.MP2, J4.A1_B12 (GND), J4.A12_B1 (GND), J4.SH1 (SHIELD), J4.SH2 (SHIELD), J4.SH3 (SHIELD), J4.SH4 (SHIELD), R1_USB.1, R2_EP_DR.1, R2_USB.2, R_TYPE_SEL.1, SJ1.1, SW_DN.1, SW_ENT.1, SW_UP.1, TP_BAT_GND.TP, U3.1 (CTG), U3.4 (GND), U3.6 (QSTRT), U3.9 (EP); also elsewhere on the board
HAPTIC_EN: IC4.A1 (EN); also elsewhere on the board
MOSI: J1.14; also elsewhere on the board
unnamed: C2-EP_DR.1, D2.1 (K), D4.2 (A)
unnamed: C2-EP_DR.2, D5.2 (A), L5.1, Q3.3 (D)
unnamed: R1_EP_DR.1, R_TYPE_SEL.2, SJ1.2
unnamed: C32.2, IC4.A2 (REG)
unnamed: EPD_C2.2, J1.4
unnamed: EPD_C1.2, J1.5
unnamed: EPD_C6.2, J1.18
unnamed: EPD_C7.2, J1.19
unnamed: EPD_C8.2, J1.20
unnamed: EPD_C10.2, J1.22
unnamed: EPD_C12.2, J1.24
unnamed: J4.A5 (CC1), R1_USB.2
unnamed: J4.B5 (CC2), R2_USB.1
OUT+: IC4.A3 (OUT+), TP_OP.TP
OUT-: IC4.C3 (OUT-), TP_ON.TP
P0.13: C30.2, R5.1, SW_UP.2; also elsewhere on the board
P0.14: C31.2, R8.1, SW_ENT.2; also elsewhere on the board
P1.01: Q1.1 (G), R_PWR_EPD.1; also elsewhere on the board
P1.02: C29.2, R7.1, SW_DN.2; also elsewhere on the board
PREVGH: D5.1 (K), EPD_C9.2, J1.21
PREVGL: D2.2 (A), EPD_C11.2, J1.23
RESE: J1.3, Q3.2 (S), R1_EP_DR.2
SCK: J1.13; also elsewhere on the board
SCL: IC4.C1 (SCL), U3.7 (SCL); also elsewhere on the board
SDA: IC4.B2 (SDA), U3.8 (SDA); also elsewhere on the board
VBAT: C27.2, TP_VBAT.TP, U3.2 (CELL), U3.3 (VDD); also elsewhere on the board
VBUS: C42.1, C43.1, D3.5 (VBUS), J4.A4_B9 (VBUS), J4.A9_B4 (VBUS); also elsewhere on the board

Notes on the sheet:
drawn by: Andreea Radu
E-Paper Drive Circuit
DMG2305UX-7
Haptic Driver
E-Paper Display Connector
Fuel Gauge
Buttons
USB C Connector & ESD Protection

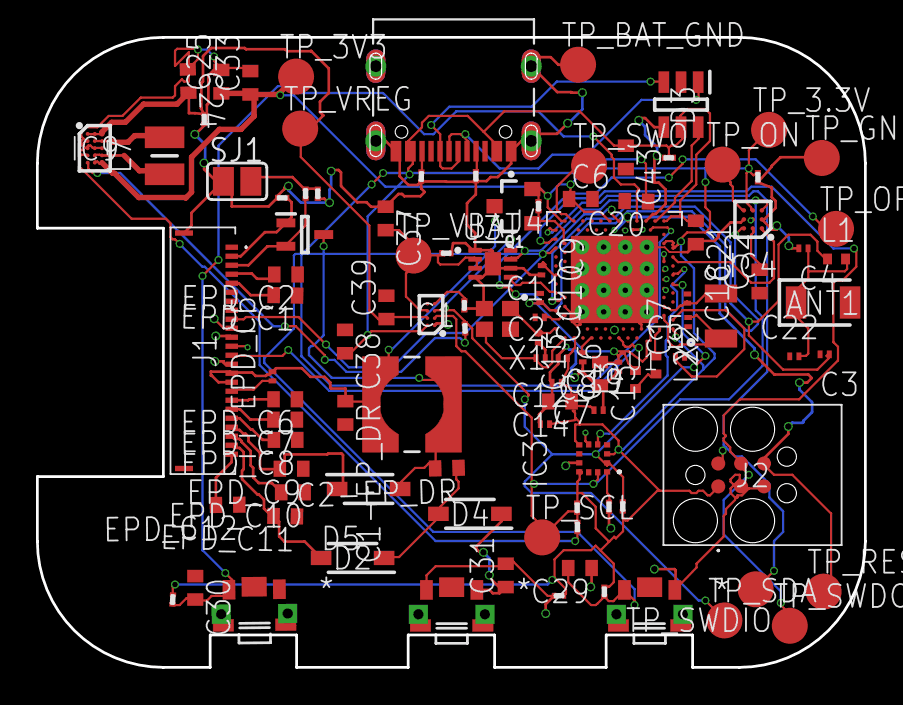
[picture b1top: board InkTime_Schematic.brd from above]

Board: 4 copper layers, 46.0 x 35.0 mm, 105 parts (0 on the bottom side), 70 nets.

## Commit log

2026-04-10 add readme
2026-04-10 readme new
2026-04-10 nou readme
2026-04-10 final readme
2026-04-10 files
2026-04-10 pictures
2026-04-10 rename

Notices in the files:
parts and their libraries:
COPYRIGHT: Copyright (C) 2024 Ultra Librarian. All rights reserved.
COPYRIGHT: Copyright (C) 2025 Ultra Librarian. All rights reserved.
